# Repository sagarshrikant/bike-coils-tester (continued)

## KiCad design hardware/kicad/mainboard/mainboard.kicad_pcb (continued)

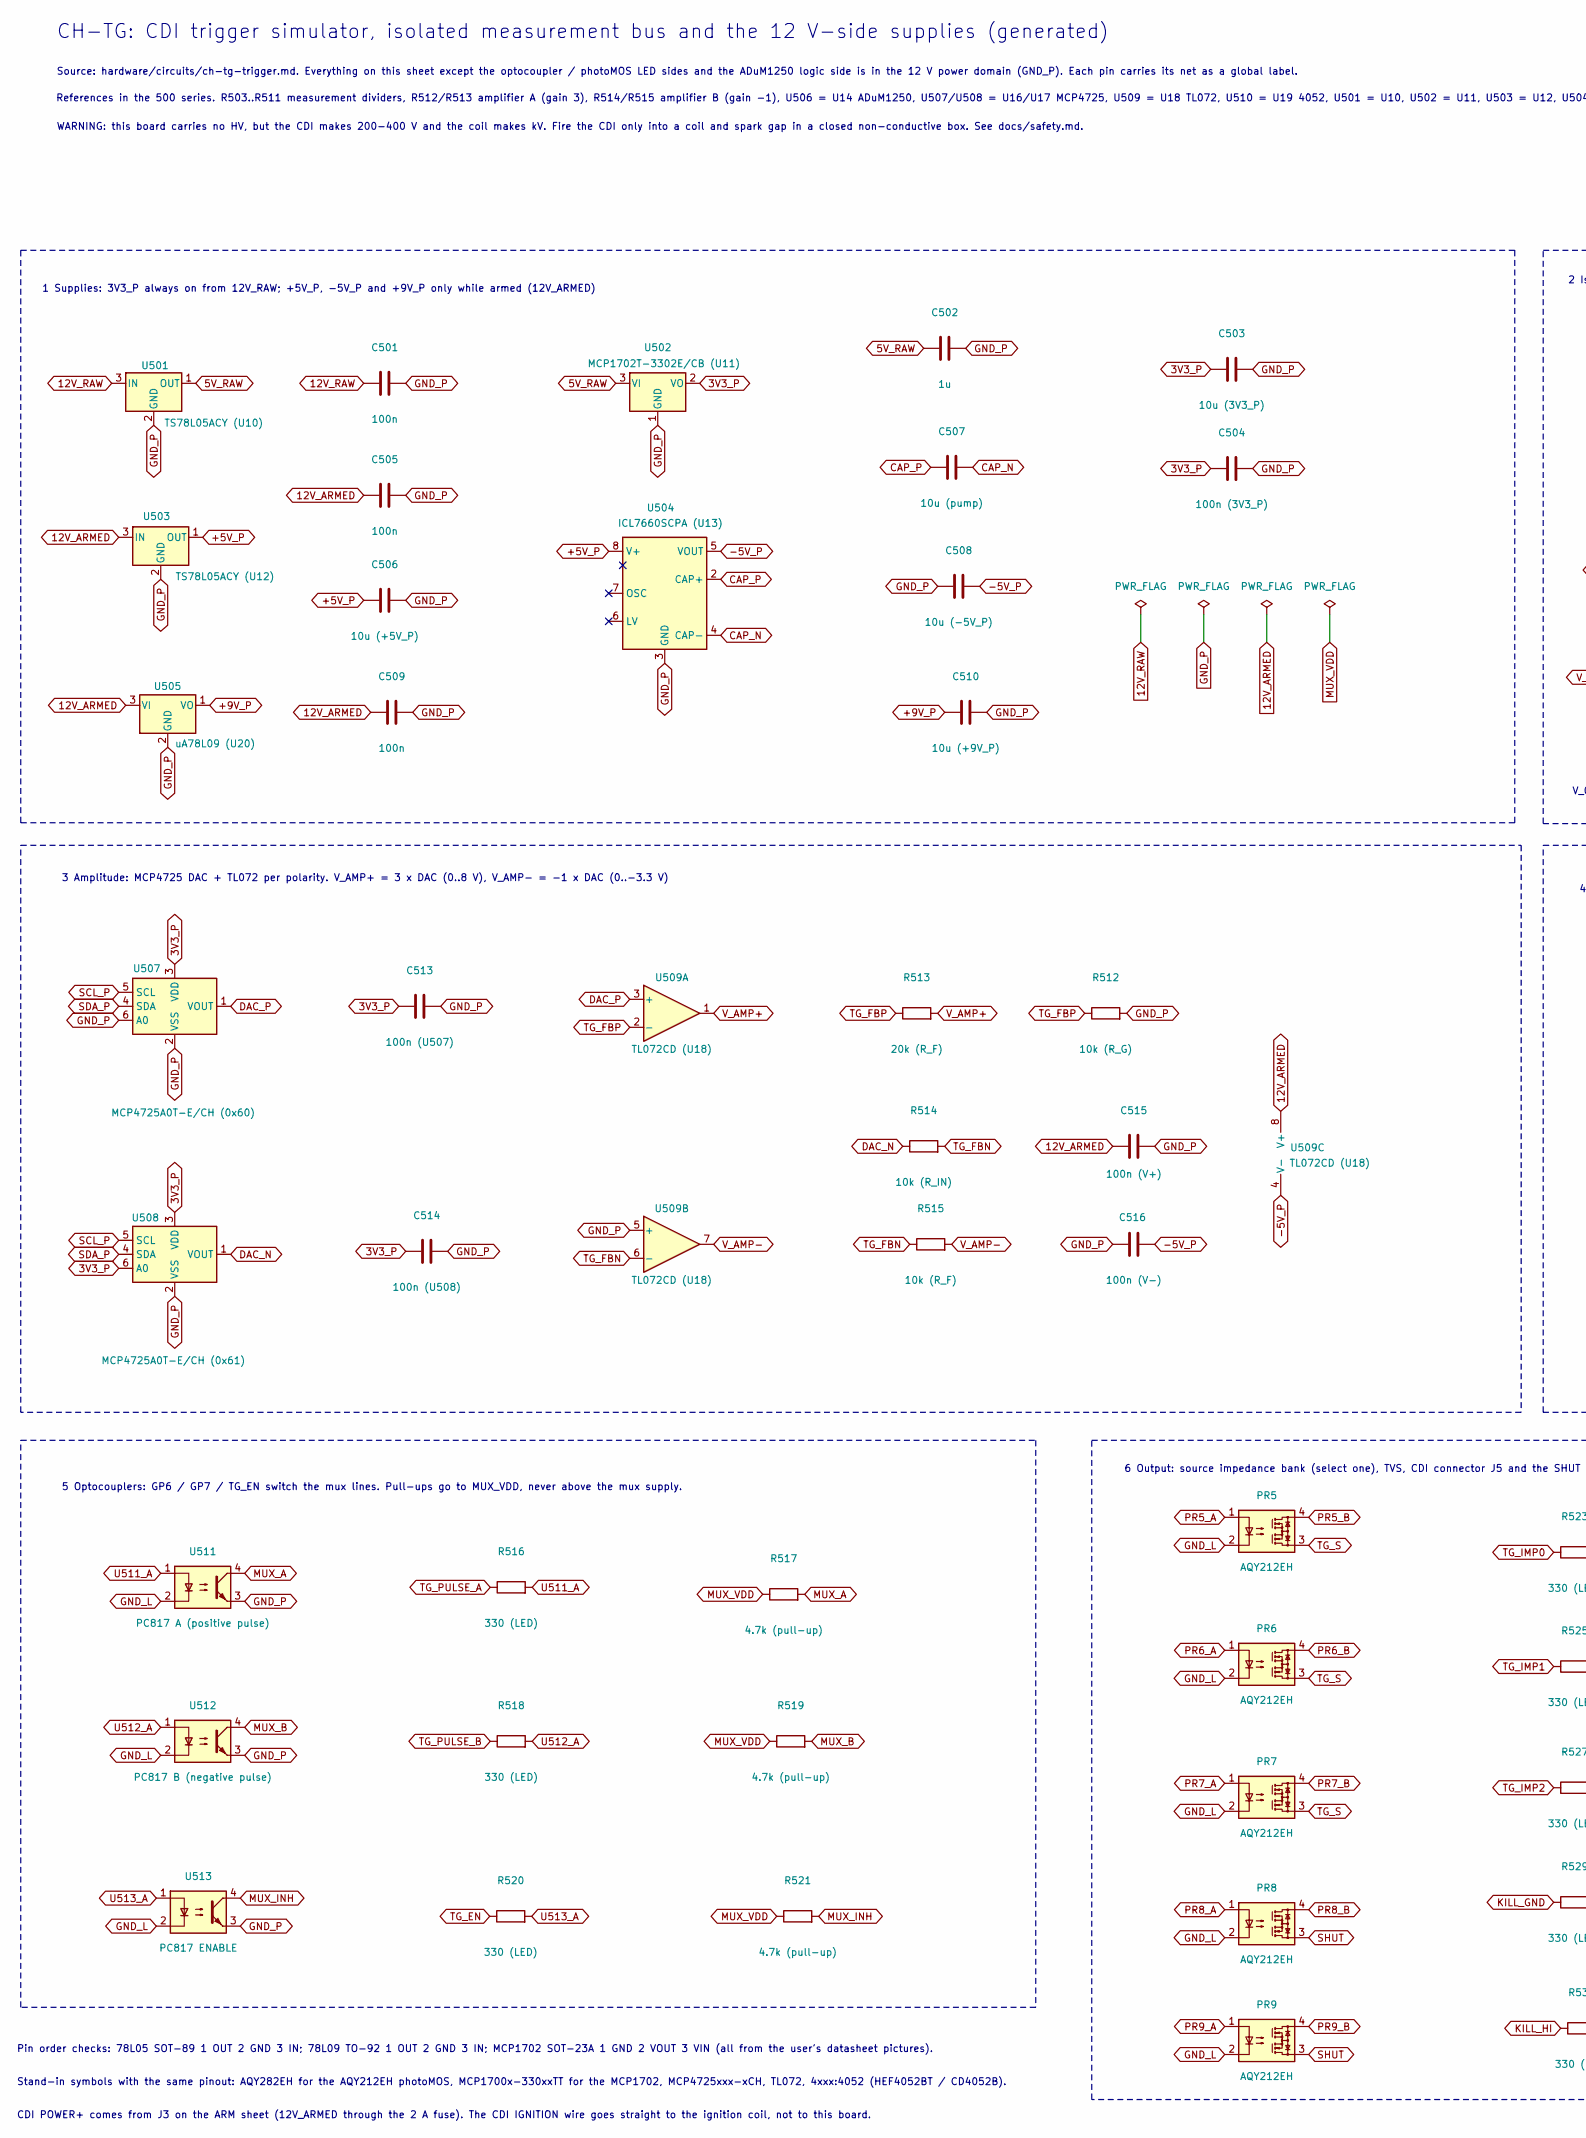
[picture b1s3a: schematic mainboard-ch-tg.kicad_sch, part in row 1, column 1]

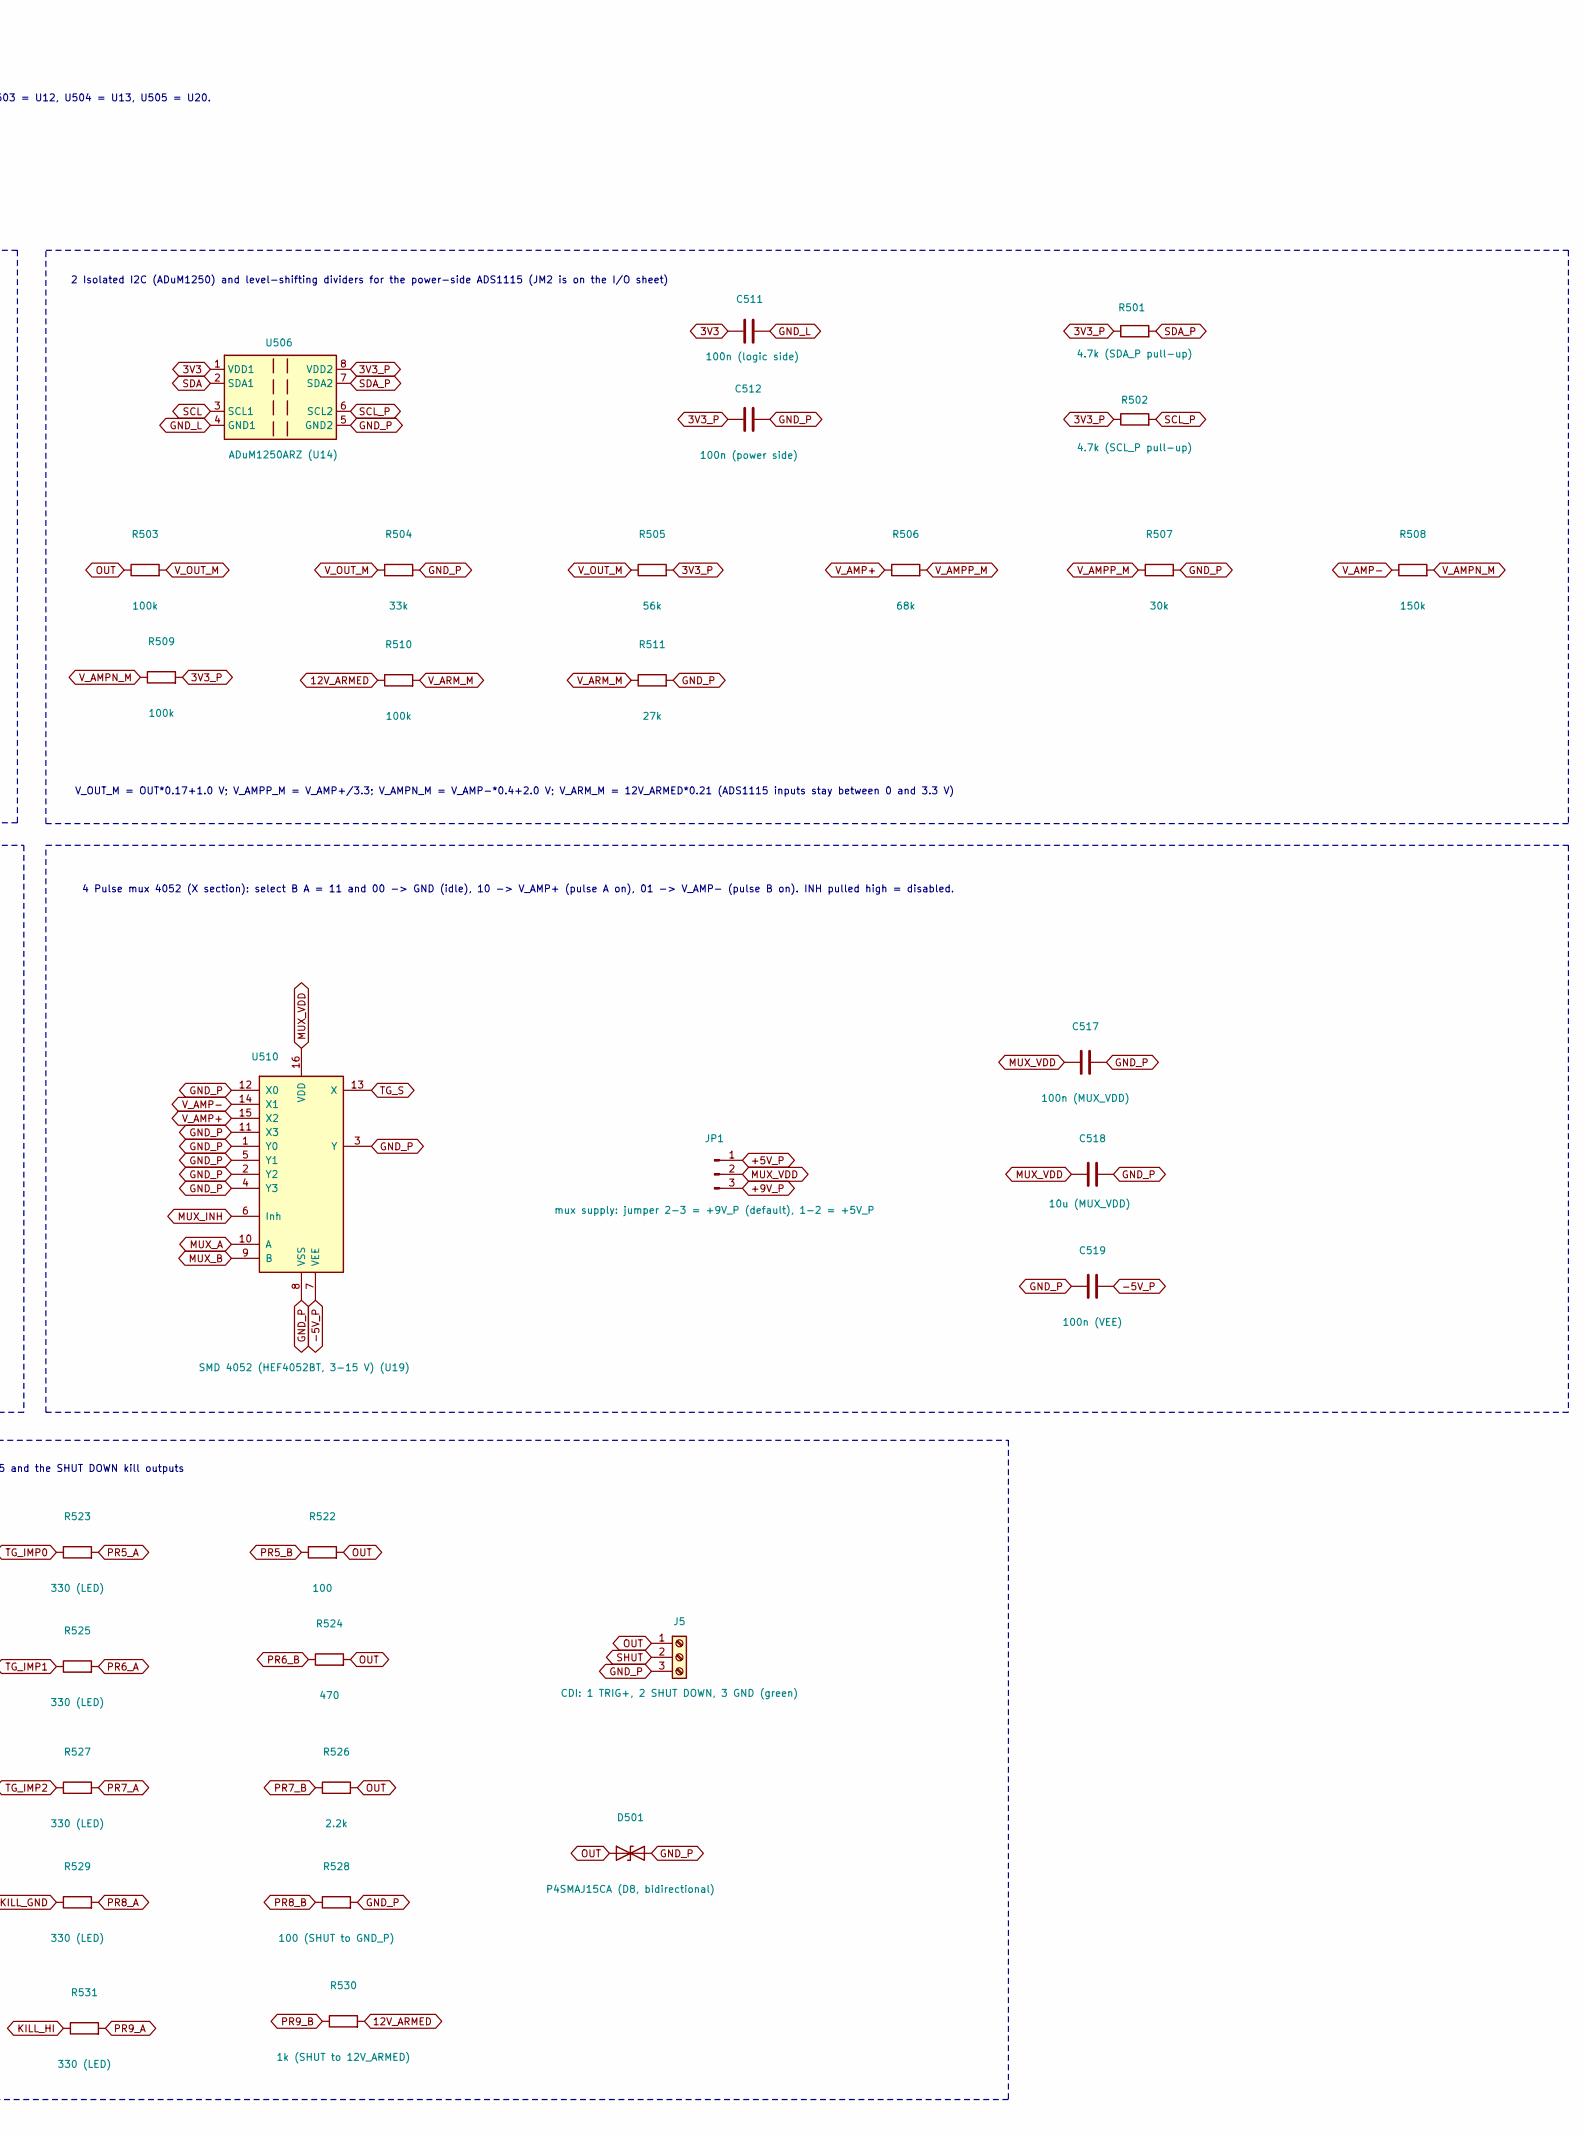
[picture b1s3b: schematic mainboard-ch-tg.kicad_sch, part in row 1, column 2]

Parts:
C501, C505, C509: 100n; C_0805_2012Metric
C502: 1u; C_0805_2012Metric
C503: 10u (3V3_P); C_0805_2012Metric
C504: 100n (3V3_P); C_0805_2012Metric
C506: 10u (+5V_P); C_0805_2012Metric
C507: 10u (pump); C_0805_2012Metric
C508: 10u (-5V_P); C_0805_2012Metric
C510: 10u (+9V_P); C_0805_2012Metric
C511: 100n (logic side); C_0805_2012Metric
C512: 100n (power side); C_0805_2012Metric
C513: 100n (U507); C_0805_2012Metric
C514: 100n (U508); C_0805_2012Metric
C515: 100n (V+); C_0805_2012Metric
C516: 100n (V-); C_0805_2012Metric
C517: 100n (MUX_VDD); C_0805_2012Metric
C518: 10u (MUX_VDD); C_0805_2012Metric
C519: 100n (VEE); C_0805_2012Metric
D501: P4SMAJ15CA (D8, bidirectional); D_SMA
J5: CDI: 1 TRIG+, 2 SHUT DOWN, 3 GND (green); TerminalBlock_Phoenix_MKDS-1,5-3-5.08_1x03_P5.08mm_Horizont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
JP1: mux supply: jumper 2-3 = +9V_P (default), 1-2 = +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; PinHeader_1x03_P2.54mm_Vertical
PR5, PR6, PR7, PR8, PR9: AQY212EH; DIP-4_W7.62mm
R501: 4.7k (SDA_P pull-up); R_0805_2012Metric
R502: 4.7k (SCL_P pull-up); R_0805_2012Metric
R503, R509, R510: 100k; R_0805_2012Metric
R504: 33k; R_0805_2012Metric
R505: 56k; R_0805_2012Metric
R506: 68k; R_0805_2012Metric
R507: 30k; R_0805_2012Metric
R508: 150k; R_0805_2012Metric
R511: 27k; R_0805_2012Metric
R512: 10k (R_G); R_0805_2012Metric
R513: 20k (R_F); R_0805_2012Metric
R514: 10k (R_IN); R_0805_2012Metric
R515: 10k (R_F); R_0805_2012Metric
R516, R518, R520, R523, R525, R527, R529, R531: 330 (LED); R_0805_2012Metric
R517, R519, R521: 4.7k (pull-up); R_0805_2012Metric
R522: 100; R_0805_2012Metric
R524: 470; R_0805_2012Metric
R526: 2.2k; R_0805_2012Metric
R528: 100 (SHUT to GND_P); R_0805_2012Metric
R530: 1k (SHUT to 12V_ARMED); R_0805_2012Metric
U501: TS78L05ACY (U10); SOT-89-3
U502: MCP1702T-3302E/CB (U11); SOT-23
U503: TS78L05ACY (U12); SOT-89-3
U504: ICL7660SCPA (U13); DIP-8_W7.62mm
U505: uA78L09 (U20); TO-92_Inline
U506: ADuM1250ARZ (U14); SOIC-8_3.9x4.9mm_P1.27mm
U507: MCP4725A0T-E/CH (0x60); SOT-23-6
U508: MCP4725A0T-E/CH (0x61); SOT-23-6
U509: TL072CD (U18); SOIC-8_3.9x4.9mm_P1.27mm
U510: SMD 4052 (HEF4052BT, 3-15 V) (U19); SOIC-16_3.9x9.9mm_P1.27mm
U511: PC817 A (positive pulse); DIP-4_in_DIP-6_socket_W7.62mm
U512: PC817 B (negative pulse); DIP-4_in_DIP-6_socket_W7.62mm
U513: PC817 ENABLE; DIP-4_in_DIP-6_socket_W7.62mm

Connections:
3V3: C511.1, U506.1 (VDD1); also elsewhere on the board
3V3_P: C503.1, C504.1, C512.1, C513.1, C514.1, R501.1, R502.1, R505.2, R509.2, U502.2 (VO), U506.8 (VDD2), U507.3 (VDD), U508.3 (VDD), U508.6 (A0); also elsewhere on the board
5V_RAW: C502.1, U501.1 (OUT), U502.3 (VI)
12V_ARMED: C505.1, C509.1, C515.1, R510.1, R530.2, U503.3 (IN), U505.3 (VI), U509.8 (V+); also elsewhere on the board
12V_RAW: C501.1, U501.3 (IN); also elsewhere on the board
+5V_P: C506.1, JP1.1, U503.1 (OUT), U504.8 (V+)
+9V_P: C510.1, JP1.3, U505.1 (VO)
-5V_P: C508.2, C516.2, C519.2, U504.5 (VOUT), U509.4 (V-), U510.7 (VEE)
CAP_N: C507.2, U504.4 (CAP-)
CAP_P: C507.1, U504.2 (CAP+)
DAC_N: R514.1, U508.1 (VOUT)
DAC_P: U507.1 (VOUT), U509.3 (+)
GND_L: C511.2, PR5.2, PR6.2, PR7.2, PR8.2, PR9.2, U506.4 (GND1), U511.2, U512.2, U513.2; also elsewhere on the board
GND_P: C501.2, C502.2, C503.2, C504.2, C505.2, C506.2, C508.1, C509.2, C510.2, C512.2, C513.2, C514.2, C515.2, C516.1, C517.2, C518.2, C519.1, D501.2 (A2), J5.3, R504.2, R507.2, R511.2, R512.2, R528.2, U501.2 (GND), U502.1 (GND), U503.2 (GND), U504.3 (GND), U505.2 (GND), U506.5 (GND2), U507.2 (VSS), U507.6 (A0), U508.2 (VSS), U509.5 (+), U510.1 (Y0), U510.2 (Y2), U510.3 (Y), U510.4 (Y3), U510.5 (Y1), U510.8 (VSS), U510.11 (X3), U510.12 (X0), U511.3, U512.3, U513.3; also elsewhere on the board
KILL_GND: R529.1; also elsewhere on the board
KILL_HI: R531.1; also elsewhere on the board
MUX_A: R517.2, U510.10 (A), U511.4
MUX_B: R519.2, U510.9 (B), U512.4
MUX_INH: R521.2, U510.6 (Inh), U513.4
MUX_VDD: C517.1, C518.1, JP1.2, R517.1, R519.1, R521.1, U510.16 (VDD)
OUT: D501.1 (A1), J5.1, R503.1, R522.2, R524.2, R526.2
PR5_A: PR5.1, R523.2
PR5_B: PR5.4, R522.1
PR6_A: PR6.1, R525.2
PR6_B: PR6.4, R524.1
PR7_A: PR7.1, R527.2
PR7_B: PR7.4, R526.1
PR8_A: PR8.1, R529.2
PR8_B: PR8.4, R528.1
PR9_A: PR9.1, R531.2
PR9_B: PR9.4, R530.1
SCL: U506.3 (SCL1); also elsewhere on the board
SCL_P: R502.2, U506.6 (SCL2), U507.5 (SCL), U508.5 (SCL); also elsewhere on the board
SDA: U506.2 (SDA1); also elsewhere on the board
SDA_P: R501.2, U506.7 (SDA2), U507.4 (SDA), U508.4 (SDA); also elsewhere on the board
SHUT: J5.2, PR8.3, PR9.3
TG_EN: R520.1; also elsewhere on the board
TG_FBN: R514.2, R515.1, U509.6 (-)
TG_FBP: R512.1, R513.1, U509.2 (-)
TG_IMP0: R523.1; also elsewhere on the board
TG_IMP1: R525.1; also elsewhere on the board
TG_IMP2: R527.1; also elsewhere on the board
TG_PULSE_A: R516.1; also elsewhere on the board
TG_PULSE_B: R518.1; also elsewhere on the board
TG_S: PR5.3, PR6.3, PR7.3, U510.13 (X)
U511_A: R516.2, U511.1
U512_A: R518.2, U512.1
U513_A: R520.2, U513.1
V_AMP+: R506.1, R513.2, U509.1, U510.15 (X2)
V_AMP-: R508.1, R515.2, U509.7, U510.14 (X1)
V_AMPN_M: R508.2, R509.1; also elsewhere on the board
V_AMPP_M: R506.2, R507.1; also elsewhere on the board
V_ARM_M: R510.2, R511.1; also elsewhere on the board
V_OUT_M: R503.2, R504.1, R505.1; also elsewhere on the board

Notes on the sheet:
5 Optocouplers: GP6 / GP7 / TG_EN switch the mux lines. Pull-ups go to MUX_VDD, never above the mux supply.
Pin order checks: 78L05 SOT-89 1 OUT 2 GND 3 IN; 78L09 TO-92 1 OUT 2 GND 3 IN; MCP1702 SOT-23A 1 GND 2 VOUT 3 VIN (all from the user's datasheet pictures).
CH-TG: CDI trigger simulator, isolated measurement bus and the 12 V-side supplies (generated)
1 Supplies: 3V3_P always on from 12V_RAW; +5V_P, -5V_P and +9V_P only while armed (12V_ARMED)
6 Output: source impedance bank (select one), TVS, CDI connector J5 and the SHUT DOWN kill outputs
2 Isolated I2C (ADuM1250) and level-shifting dividers for the power-side ADS1115 (JM2 is on the I/O sheet)
WARNING: this board carries no HV, but the CDI makes 200-400 V and the coil makes kV. Fire the CDI only into a coil and spark gap in a closed non-conductive box. See docs/safety.md.
4 Pulse mux 4052 (X section): select B A = 11 and 00 -> GND (idle), 10 -> V_AMP+ (pulse A on), 01 -> V_AMP- (pulse B on). INH pulled high = disabled.
References in the 500 series. R503..R511 measurement dividers, R512/R513 amplifier A (gain 3), R514/R515 amplifier B (gain -1), U506 = U14 ADuM1250, U507/U508 = U16/U17 MCP4725, U509 = U18 TL072, U510 = U19 4052, U501 = U10, U502 = U11, U503 = U12, U504 = U13, U505 = U20.
3 Amplitude: MCP4725 DAC + TL072 per polarity. V_AMP+ = 3 x DAC (0..8 V), V_AMP- = -1 x DAC (0..-3.3 V)
Source: hardware/circuits/ch-tg-trigger.md. Everything on this sheet except the optocoupler / photoMOS LED sides and the ADuM1250 logic side is in the 12 V power domain (GND_P). Each pin carries its net as a global label.
Stand-in symbols with the same pinout: AQY282EH for the AQY212EH photoMOS, MCP1700x-330xxTT for the MCP1702, MCP4725xxx-xCH, TL072, 4xxx:4052 (HEF4052BT / CD4052B).
V_OUT_M = OUT*0.17+1.0 V; V_AMPP_M = V_AMP+/3.3; V_AMPN_M = V_AMP-*0.4+2.0 V; V_ARM_M = 12V_ARMED*0.21 (ADS1115 inputs stay between 0 and 3.3 V)
CDI POWER+ comes from J3 on the ARM sheet (12V_ARMED through the 2 A fuse). The CDI IGNITION wire goes straight to the ignition coil, not to this board.

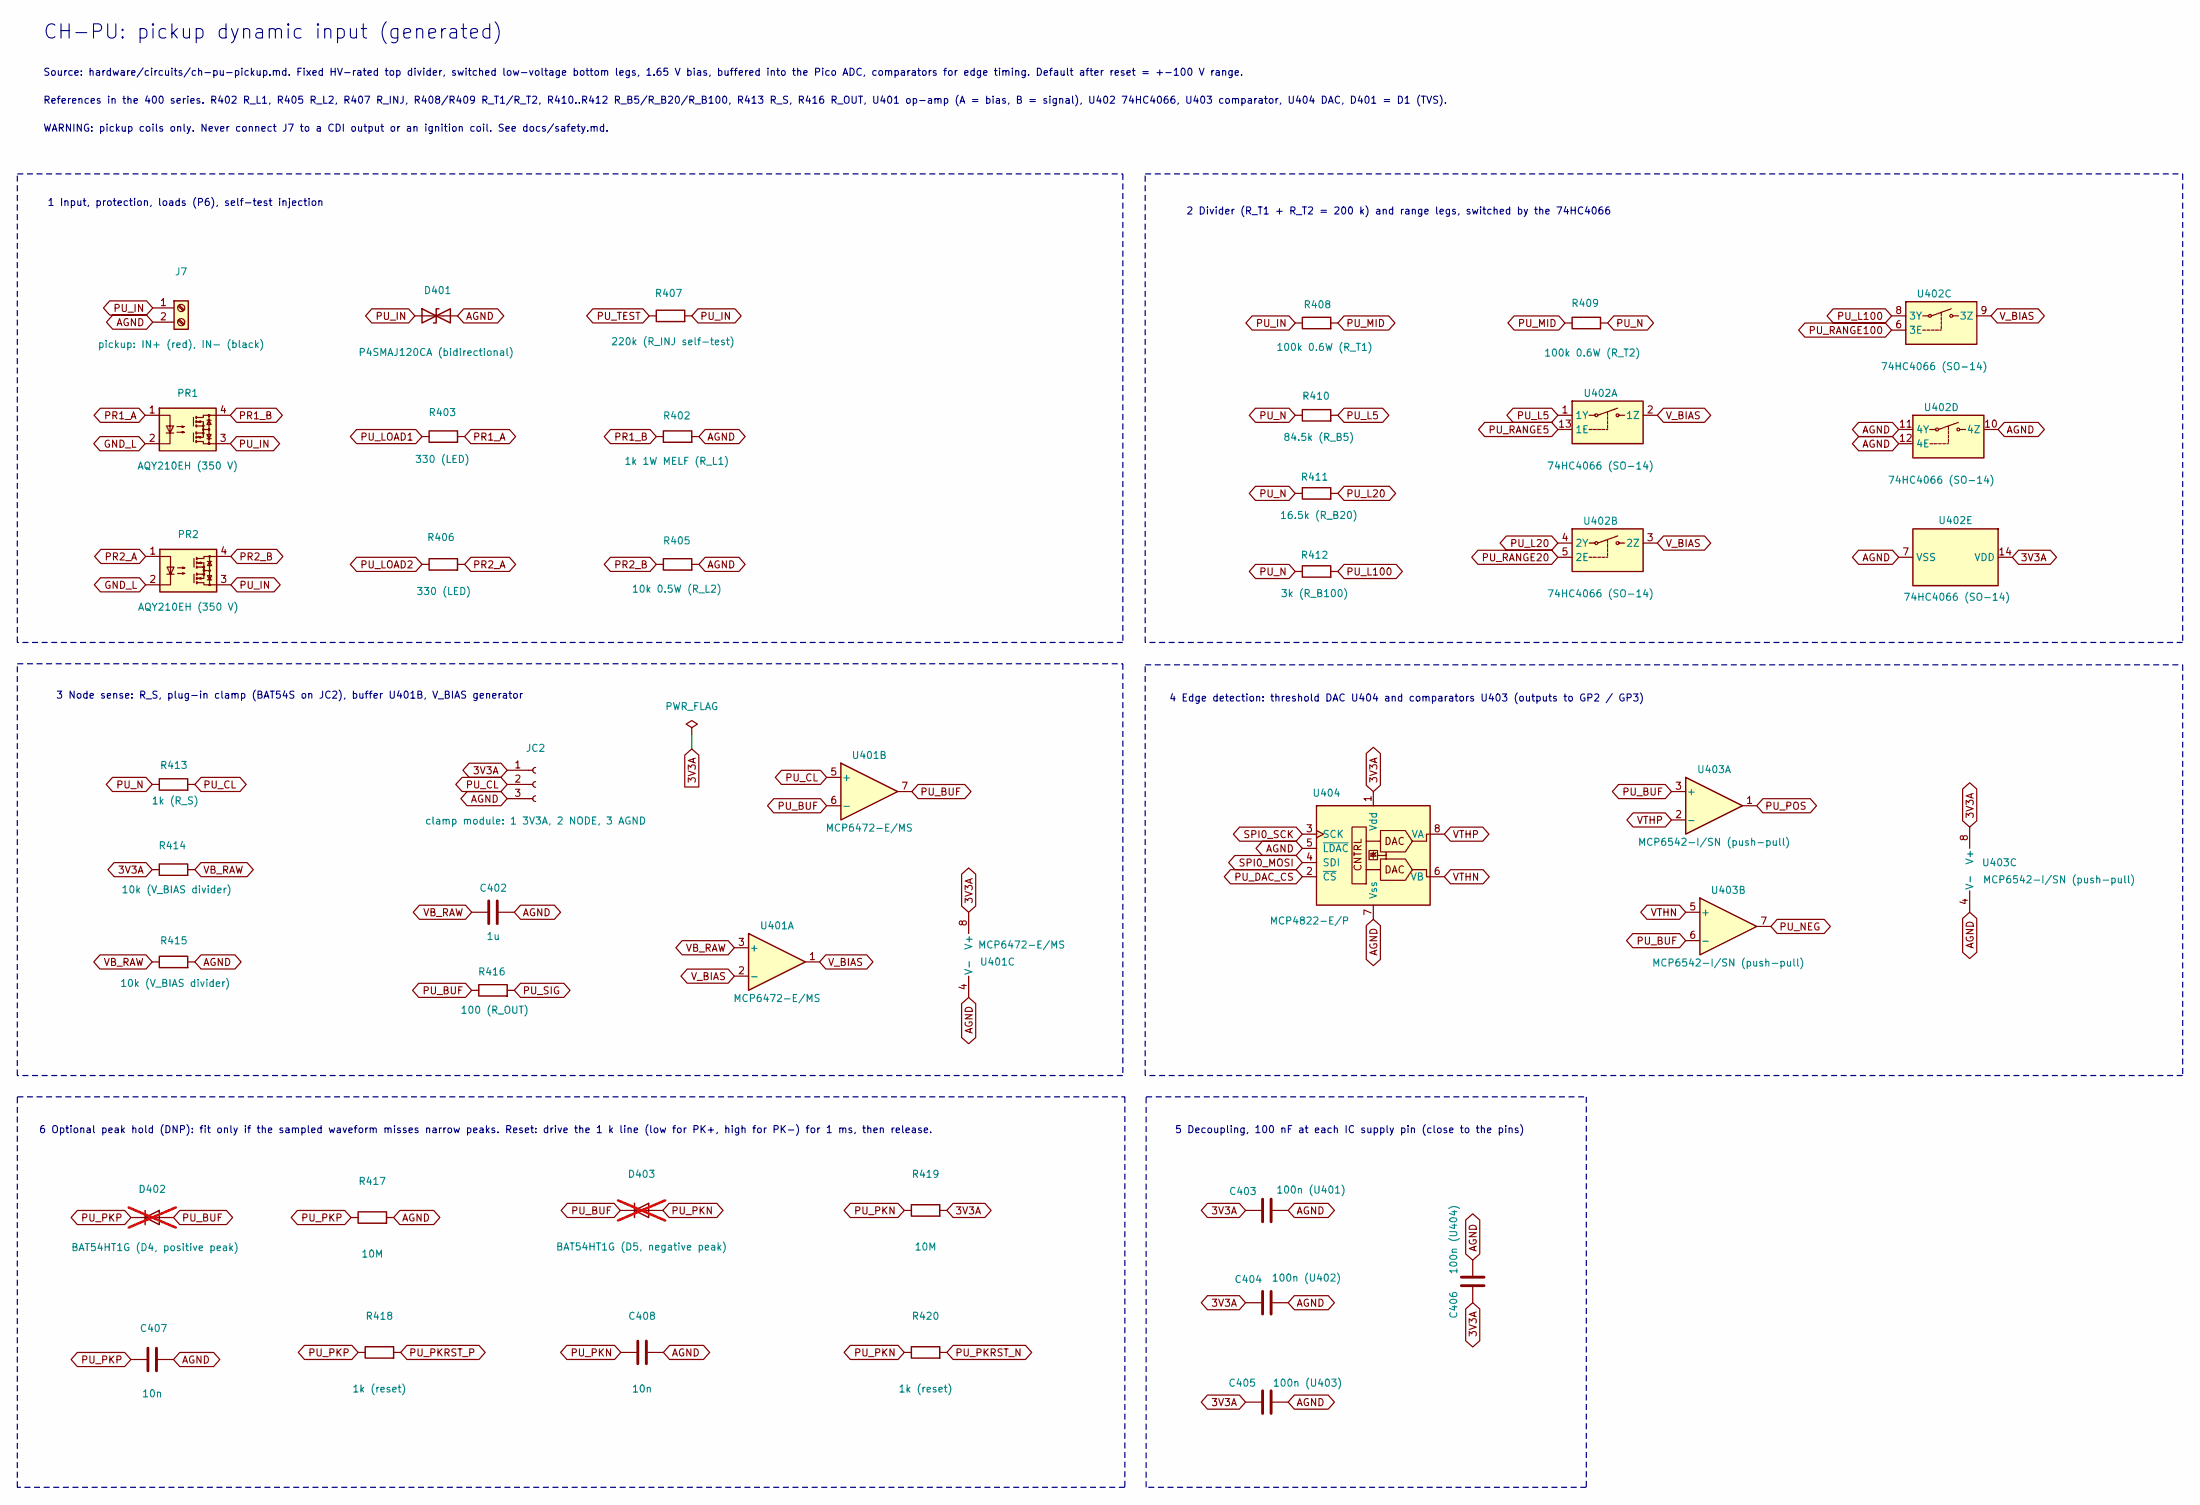
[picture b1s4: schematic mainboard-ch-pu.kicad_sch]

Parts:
C402: 1u; C_0805_2012Metric
C403: 100n (U401); C_0805_2012Metric
C404: 100n (U402); C_0805_2012Metric
C405: 100n (U403); C_0805_2012Metric
C406: 100n (U404); C_0805_2012Metric
C407, C408: 10n; C_0805_2012Metric
D401: P4SMAJ120CA (bidirectional); D_SMA
D402: BAT54HT1G (D4, positive peak); D_SOD-323; not fitted
D403: BAT54HT1G (D5, negative peak); D_SOD-323; not fitted
J7: pickup: IN+ (red), IN- (black); TerminalBlock_Phoenix_MKDS-1,5-2-5.08_1x02_P5.08mm_Horizont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
JC2: clamp module: 1 3V3A, 2 NODE, 3 AGND; PinSocket_1x03_P2.54mm_Vertical
PR1, PR2: AQY210EH (350 V); DIP-4_W7.62mm
R402: 1k 1W MELF (R_L1); R_MELF_MMB-0207
R403, R406: 330 (LED); R_0805_2012Metric
R405: 10k 0.5W (R_L2); R_Axial_DIN0207_L6.3mm_D2.5mm_P10.16mm_Horizontal
R407: 220k (R_INJ self-test); R_0805_2012Metric
R408: 100k 0.6W (R_T1); R_Axial_DIN0207_L6.3mm_D2.5mm_P10.16mm_Horizontal
R409: 100k 0.6W (R_T2); R_Axial_DIN0207_L6.3mm_D2.5mm_P10.16mm_Horizontal
R410: 84.5k (R_B5); R_0805_2012Metric
R411: 16.5k (R_B20); R_0805_2012Metric
R412: 3k (R_B100); R_0805_2012Metric
R413: 1k (R_S); R_0805_2012Metric
R414, R415: 10k (V_BIAS divider); R_0805_2012Metric
R416: 100 (R_OUT); R_0805_2012Metric
R417, R419: 10M; R_0805_2012Metric
R418, R420: 1k (reset); R_0805_2012Metric
U401: MCP6472-E/MS; MSOP-8_3x3mm_P0.65mm
U402: 74HC4066 (SO-14); SOIC-14_3.9x8.7mm_P1.27mm
U403: MCP6542-I/SN (push-pull); SOIC-8_3.9x4.9mm_P1.27mm
U404: MCP4822-E/P; DIP-8_W7.62mm

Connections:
3V3A: C403.1, C404.1, C405.1, C406.1, JC2.1, R414.1, R419.2, U401.8 (V+), U402.14 (VDD), U403.8 (V+), U404.1 (Vdd); also elsewhere on the board
AGND: C402.2, C403.2, C404.2, C405.2, C406.2, C407.2, C408.2, D401.2 (A2), J7.2, JC2.3, R402.2, R405.2, R415.2, R417.2, U401.4 (V-), U402.7 (VSS), U402.10 (4Z), U402.11 (4Y), U402.12 (4E), U403.4 (V-), U404.5 (~LDAC), U404.7 (Vss); also elsewhere on the board
GND_L: PR1.2, PR2.2; also elsewhere on the board
PR1_A: PR1.1, R403.2
PR1_B: PR1.4, R402.1
PR2_A: PR2.1, R406.2
PR2_B: PR2.4, R405.1
PU_BUF: D402.2 (A), D403.1 (K), R416.1, U401.6 (-), U401.7, U403.3 (+), U403.6 (-)
PU_CL: JC2.2, R413.2, U401.5 (+)
PU_DAC_CS: U404.2 (~CS); also elsewhere on the board
PU_IN: D401.1 (A1), J7.1, PR1.3, PR2.3, R407.2, R408.1
PU_L5: R410.2, U402.1 (1Y)
PU_L20: R411.2, U402.4 (2Y)
PU_L100: R412.2, U402.8 (3Y)
PU_LOAD1: R403.1; also elsewhere on the board
PU_LOAD2: R406.1; also elsewhere on the board
PU_MID: R408.2, R409.1
PU_N: R409.2, R410.1, R411.1, R412.1, R413.1
PU_NEG: U403.7; also elsewhere on the board
PU_PKN: C408.1, D403.2 (A), R419.1, R420.1; also elsewhere on the board
PU_PKP: C407.1, D402.1 (K), R417.1, R418.1; also elsewhere on the board
PU_PKRST_N: R420.2; also elsewhere on the board
PU_PKRST_P: R418.2; also elsewhere on the board
PU_POS: U403.1; also elsewhere on the board
PU_RANGE5: U402.13 (1E); also elsewhere on the board
PU_RANGE20: U402.5 (2E); also elsewhere on the board
PU_RANGE100: U402.6 (3E); also elsewhere on the board
PU_SIG: R416.2; also elsewhere on the board
PU_TEST: R407.1; also elsewhere on the board
SPI0_MOSI: U404.4 (SDI); also elsewhere on the board
SPI0_SCK: U404.3 (SCK); also elsewhere on the board
VB_RAW: C402.1, R414.2, R415.1, U401.3 (+)
VTHN: U403.5 (+), U404.6 (VB)
VTHP: U403.2 (-), U404.8 (VA)
V_BIAS: U401.1, U401.2 (-), U402.2 (1Z), U402.3 (2Z), U402.9 (3Z)

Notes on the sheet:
5 Decoupling, 100 nF at each IC supply pin (close to the pins)
WARNING: pickup coils only. Never connect J7 to a CDI output or an ignition coil. See docs/safety.md.
4 Edge detection: threshold DAC U404 and comparators U403 (outputs to GP2 / GP3)
CH-PU: pickup dynamic input (generated)
1 Input, protection, loads (P6), self-test injection
6 Optional peak hold (DNP): fit only if the sampled waveform misses narrow peaks. Reset: drive the 1 k line (low for PK+, high for PK-) for 1 ms, then release.
Source: hardware/circuits/ch-pu-pickup.md. Fixed HV-rated top divider, switched low-voltage bottom legs, 1.65 V bias, buffered into the Pico ADC, comparators for edge timing. Default after reset = +-100 V range.
3 Node sense: R_S, plug-in clamp (BAT54S on JC2), buffer U401B, V_BIAS generator
2 Divider (R_T1 + R_T2 = 200 k) and range legs, switched by the 74HC4066
References in the 400 series. R402 R_L1, R405 R_L2, R407 R_INJ, R408/R409 R_T1/R_T2, R410..R412 R_B5/R_B20/R_B100, R413 R_S, R416 R_OUT, U401 op-amp (A = bias, B = signal), U402 74HC4066, U403 comparator, U404 DAC, D401 = D1 (TVS).

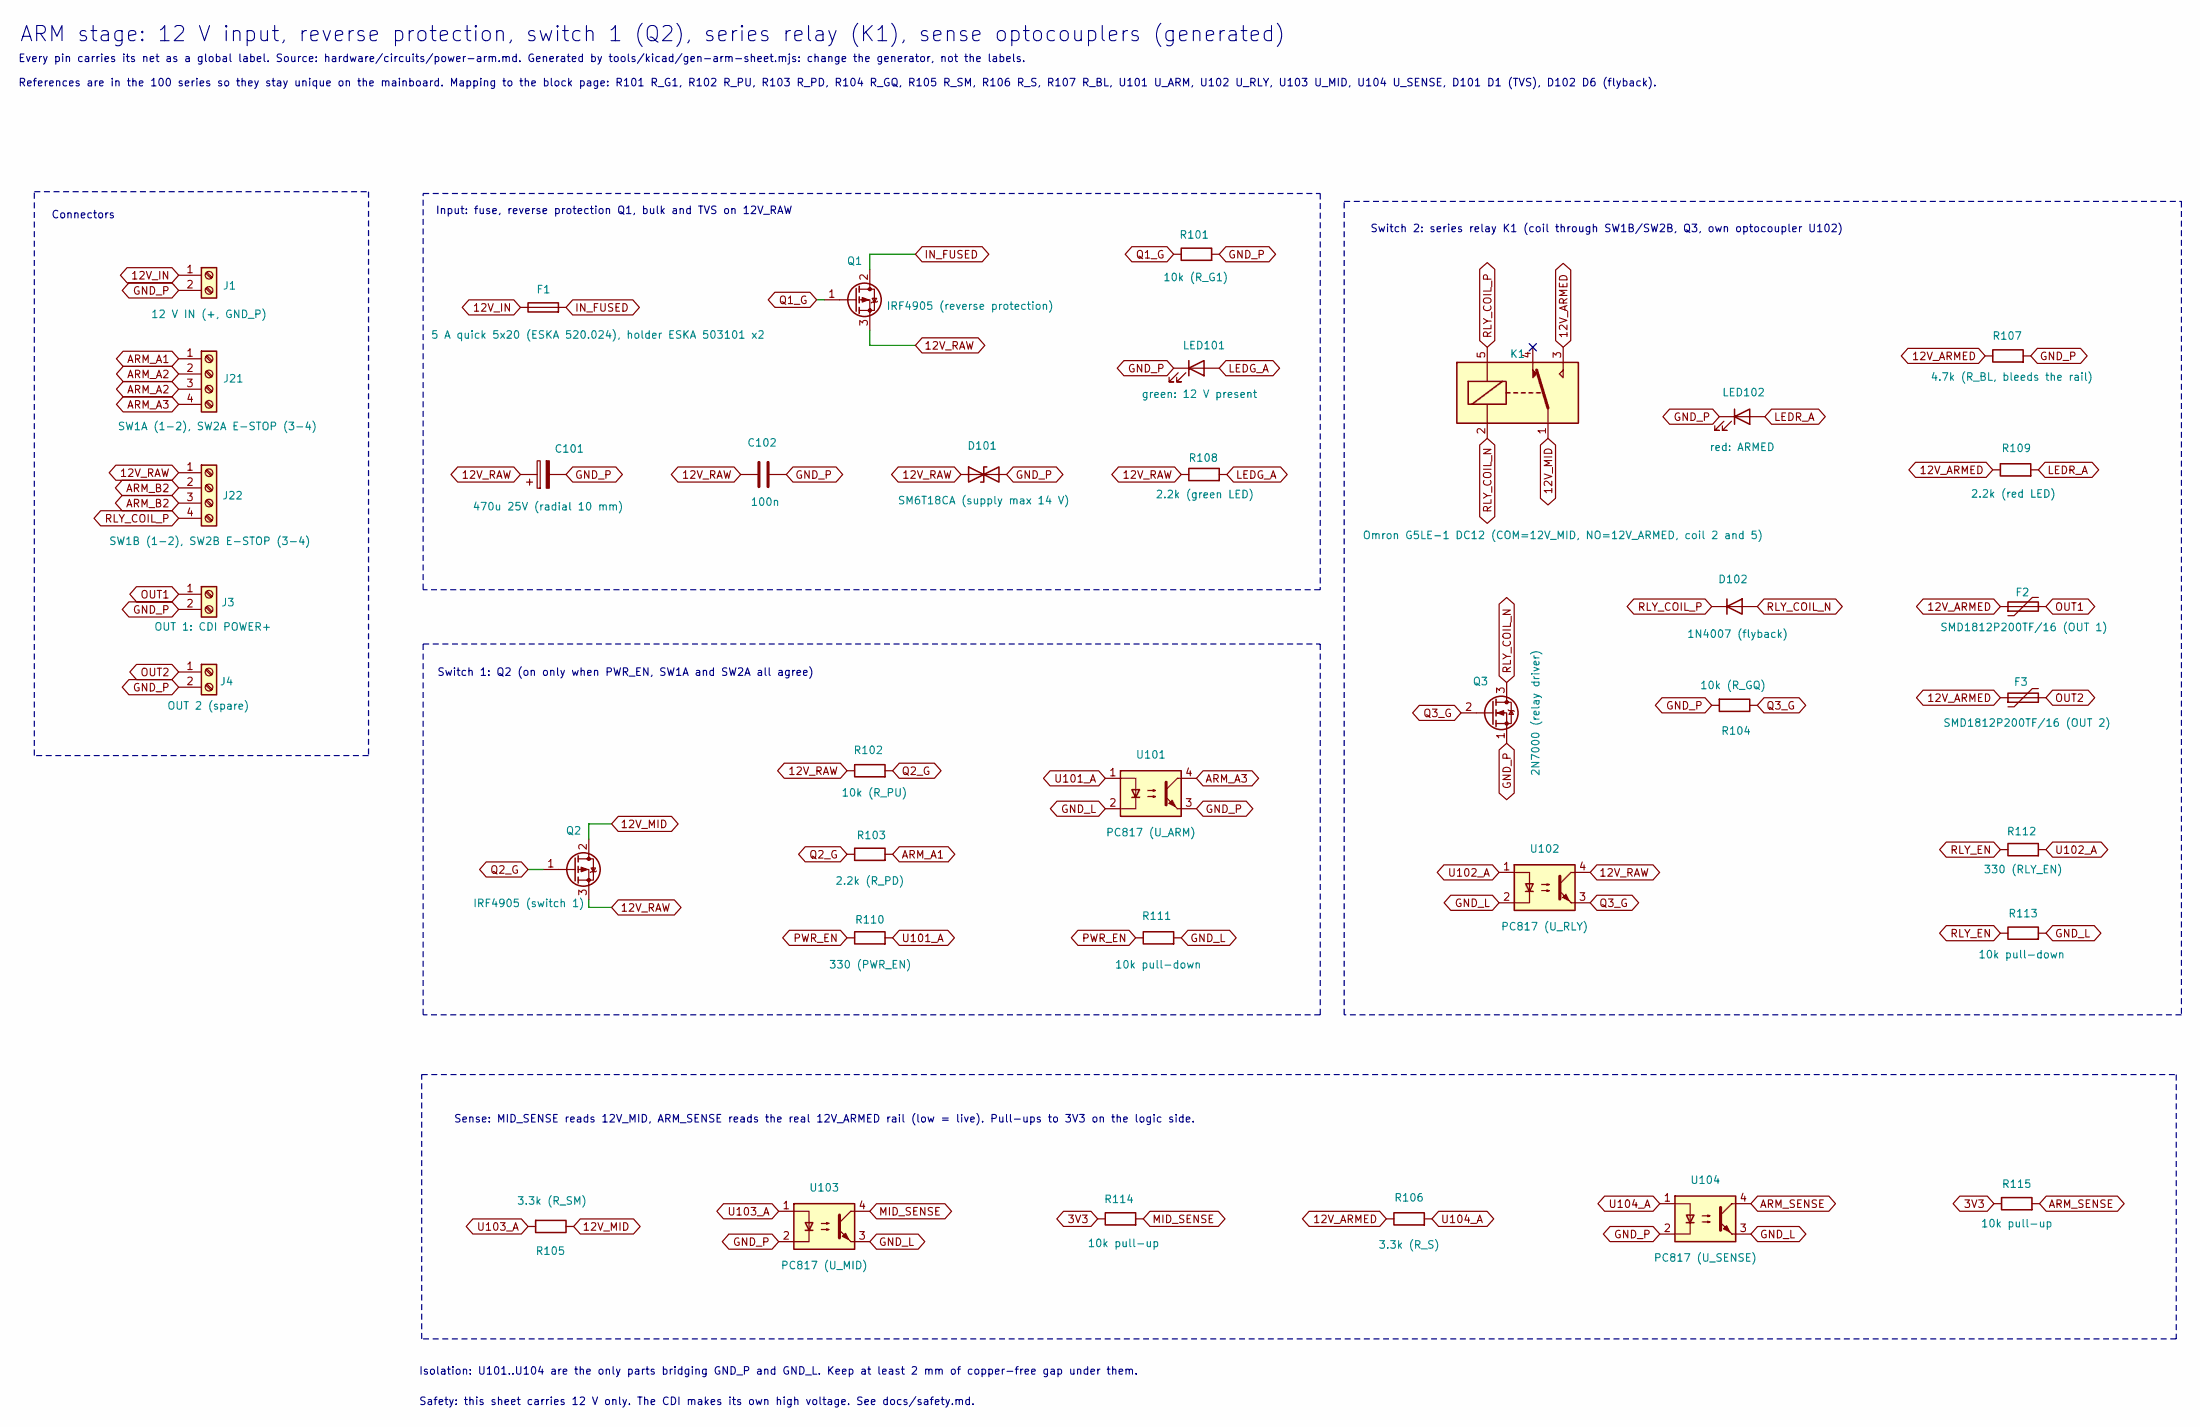
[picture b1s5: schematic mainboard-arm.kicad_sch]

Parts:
C101: 470u 25V (radial 10 mm); CP_Radial_D10.0mm_P5.00mm
C102: 100n; C_0805_2012Metric
D101: SM6T18CA (supply max 14 V); D_SMB
D102: 1N4007 (flyback); D_DO-41_SOD81_P10.16mm_Horizontal
F1: 5 A quick 5x20 (ESKA 520.024), holder ESKA 503101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; Fuseholder_ESKA_503101
F2: SMD1812P200TF/16 (OUT 1); Fuse_1812_4532Metric
F3: SMD1812P200TF/16 (OUT 2); Fuse_1812_4532Metric
J1: 12 V IN (+, GND_P); TerminalBlock_Phoenix_MKDS-1,5-2-5.08_1x02_P5.08mm_Horizont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
J3: OUT 1: CDI POWER+; TerminalBlock_Phoenix_MKDS-1,5-2-5.08_1x02_P5.08mm_Horizont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
J4: OUT 2 (spare); TerminalBlock_Phoenix_MKDS-1,5-2-5.08_1x02_P5.08mm_Horizont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
J21: SW1A (1-2), SW2A E-STOP (3-4); TerminalBlock_Phoenix_MKDS-1,5-4-5.08_1x04_P5.08mm_Horizont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
J22: SW1B (1-2), SW2B E-STOP (3-4); TerminalBlock_Phoenix_MKDS-1,5-4-5.08_1x04_P5.08mm_Horizont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
K1: Omron G5LE-1 DC12 (COM=12V_MID, NO=12V_ARMED, coi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; Relay_SPDT_Omron-G5LE-1
LED101: green: 12 V present; LED_D3.0mm
LED102: red: ARMED; LED_D3.0mm
Q1: IRF4905 (reverse protection); TO-220-3_Vertical
Q2: IRF4905 (switch 1); TO-220-3_Vertical
Q3: 2N7000 (relay driver); TO-92_Inline
R101: 10k (R_G1); R_0805_2012Metric
R102: 10k (R_PU); R_0805_2012Metric
R103: 2.2k (R_PD); R_0805_2012Metric
R104: 10k (R_GQ); R_0805_2012Metric
R105: 3.3k (R_SM); R_0805_2012Metric
R106: 3.3k (R_S); R_0805_2012Metric
R107: 4.7k (R_BL, bleeds the rail); R_0805_2012Metric
R108: 2.2k (green LED); R_0805_2012Metric
R109: 2.2k (red LED); R_0805_2012Metric
R110: 330 (PWR_EN); R_0805_2012Metric
R111, R113: 10k pull-down; R_0805_2012Metric
R112: 330 (RLY_EN); R_0805_2012Metric
R114, R115: 10k pull-up; R_0805_2012Metric
U101: PC817 (U_ARM); DIP-4_in_DIP-6_socket_W7.62mm
U102: PC817 (U_RLY); DIP-4_in_DIP-6_socket_W7.62mm
U103: PC817 (U_MID); DIP-4_in_DIP-6_socket_W7.62mm
U104: PC817 (U_SENSE); DIP-4_in_DIP-6_socket_W7.62mm

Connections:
3V3: R114.1, R115.1; also elsewhere on the board
12V_ARMED: F2.1, F3.1, K1.3, R106.1, R107.1, R109.1; also elsewhere on the board
12V_IN: F1.1, J1.1
12V_MID: K1.1, Q2.2 (D), R105.1
12V_RAW: C101.1, C102.1, D101.1 (A1), J22.1, Q1.3 (S), Q2.3 (S), R102.1, R108.1, U102.4; also elsewhere on the board
ARM_A1: J21.1, R103.2
ARM_A2: J21.2, J21.3
ARM_A3: J21.4, U101.4
ARM_B2: J22.2, J22.3
ARM_SENSE: R115.2, U104.4; also elsewhere on the board
GND_L: R111.2, R113.2, U101.2, U102.2, U103.3, U104.3; also elsewhere on the board
GND_P: C101.2, C102.2, D101.2 (A2), J1.2, J3.2, J4.2, LED101.1 (K), LED102.1 (K), Q3.1 (S), R101.2, R104.2, R107.2, U101.3, U103.2, U104.2; also elsewhere on the board
IN_FUSED: F1.2, Q1.2 (D)
LEDG_A: LED101.2 (A), R108.2
LEDR_A: LED102.2 (A), R109.2
MID_SENSE: R114.2, U103.4; also elsewhere on the board
OUT1: F2.2, J3.1
OUT2: F3.2, J4.1
PWR_EN: R110.1, R111.1; also elsewhere on the board
Q1_G: Q1.1 (G), R101.1
Q2_G: Q2.1 (G), R102.2, R103.1
Q3_G: Q3.2 (G), R104.1, U102.3
RLY_COIL_N: D102.2 (A), K1.2, Q3.3 (D)
RLY_COIL_P: D102.1 (K), J22.4, K1.5
RLY_EN: R112.1, R113.1; also elsewhere on the board
U101_A: R110.2, U101.1
U102_A: R112.2, U102.1
U103_A: R105.2, U103.1
U104_A: R106.2, U104.1

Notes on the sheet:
Safety: this sheet carries 12 V only. The CDI makes its own high voltage. See docs/safety.md.
Input: fuse, reverse protection Q1, bulk and TVS on 12V_RAW
Every pin carries its net as a global label. Source: hardware/circuits/power-arm.md. Generated by tools/kicad/gen-arm-sheet.mjs: change the generator, not the labels.
Switch 1: Q2 (on only when PWR_EN, SW1A and SW2A all agree)
References are in the 100 series so they stay unique on the mainboard. Mapping to the block page: R101 R_G1, R102 R_PU, R103 R_PD, R104 R_GQ, R105 R_SM, R106 R_S, R107 R_BL, U101 U_ARM, U102 U_RLY, U103 U_MID, U104 U_SENSE, D101 D1 (TVS), D102 D6 (flyback).
Switch 2: series relay K1 (coil through SW1B/SW2B, Q3, own optocoupler U102)
Connectors
ARM stage: 12 V input, reverse protection, switch 1 (Q2), series relay (K1), sense optocouplers (generated)
Sense: MID_SENSE reads 12V_MID, ARM_SENSE reads the real 12V_ARMED rail (low = live). Pull-ups to 3V3 on the logic side.
Isolation: U101..U104 are the only parts bridging GND_P and GND_L. Keep at least 2 mm of copper-free gap under them.
